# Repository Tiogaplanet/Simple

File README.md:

# Simple

 Simple - The Arduino UNO-compatible development system
 
 Created using pin-through hole (PTH) components, Simple is meant to be easy to assemble and modify.  This repository contains the Eagle files necessary to order the printed circuit board.

Based on Sparkfun's retired RedBoard PTH kit.

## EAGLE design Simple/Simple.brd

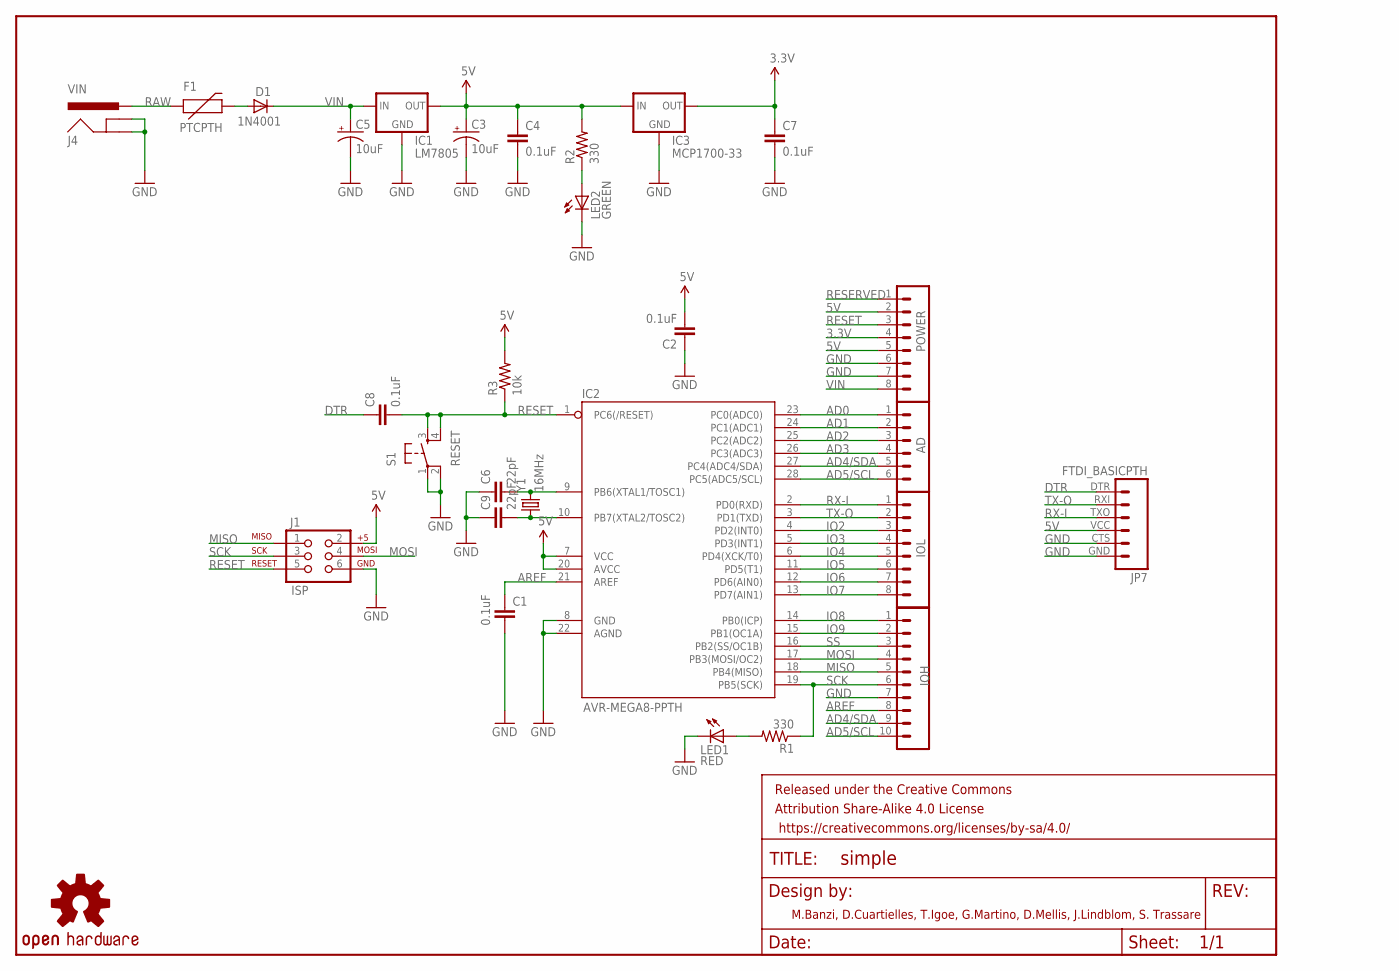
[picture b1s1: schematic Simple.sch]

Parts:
AD: M06SIP; 1X06
C1, C2, C4, C7, C8: 0.1uF; CAP-PTH-SMALL2
C3, C5: 10uF; CPOL-RADIAL-10UF-25V
C6, C9: 22pF; CAP-PTH-SMALL2
D1: 1N4001; DIODE-1N4001
F1: PTCPTH; PTC
FRAME2: FRAME-LETTER; CREATIVE_COMMONS
IC1: LM7805; TO-220-ALT
IC2: AVR-MEGA8-PPTH; DIL28-3
IC3: MCP1700-33; TO-92
IOH: IOH; 1X10
IOL: M081X08; 1X08
J1: ISP; 2X3
J4: VIN; POWER_JACK_PTH_LOCK
JP7: FTDI_BASICPTH; FTDI_BASIC
LED1: RED; LED5MM
LED2: GREEN; LED5MM
POWER: POWER; 1X08
R1, R2: 330; AXIAL-0.3
R3: 10k; AXIAL-0.3
S1: RESET; TACTILE-PTH
U$7: OSHW-LOGOM; OSHW-LOGO-M
Y1: 16MHz; HC49US

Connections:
3.3V: C7.1, IC3.3 (OUT), POWER.4
5V: C2.2, C3.1 (+), C4.1, IC1.OUT, IC2.7 (VCC), IC2.20 (AVCC), IC3.2 (IN), J1.2, JP7.VCC (4), POWER.5, R2.P$2 (2), R3.P$2 (2)
AD0: AD.1, IC2.23 (PC0(ADC0))
AD1: AD.2, IC2.24 (PC1(ADC1))
AD2: AD.3, IC2.25 (PC2(ADC2))
AD3: AD.4, IC2.26 (PC3(ADC3))
AD4/SDA: AD.5, IC2.27 (PC4(ADC4/SDA)), IOH.9
AD5/SCL: AD.6, IC2.28 (PC5(ADC5/SCL)), IOH.10
AREF: C1.1, IC2.21 (AREF), IOH.8
DTR: C8.1, JP7.DTR (1)
GND: C1.2, C2.1, C3.2 (-), C4.2, C5.2 (-), C6.1, C7.2, C9.1, IC1.GND, IC2.8 (GND), IC2.22 (AGND), IC3.1 (GND), IOH.7, J1.6, J4.GND, J4.GNDBREAK, JP7.CTS (5), JP7.GND (6), LED1.K (C), LED2.K (C), POWER.6, POWER.7, S1.1, S1.2
IO2: IC2.4 (PD2(INT0)), IOL.3
IO3: IC2.5 (PD3(INT1)), IOL.4
IO4: IC2.6 (PD4(XCK/T0)), IOL.5
IO5: IC2.11 (PD5(T1)), IOL.6
IO6: IC2.12 (PD6(AIN0)), IOL.7
IO7: IC2.13 (PD7(AIN1)), IOL.8
IO8: IC2.14 (PB0(ICP)), IOH.1
IO9: IC2.15 (PB1(OC1A)), IOH.2
MISO: IC2.18 (PB4(MISO)), IOH.5, J1.1
MOSI: IC2.17 (PB3(MOSI/OC2)), IOH.4, J1.4
unnamed: LED1.A, R1.P$2 (2)
unnamed: LED2.A, R2.P$1 (1)
unnamed: C6.2, IC2.9 (PB6(XTAL1/TOSC1)), Y1.2
unnamed: C9.2, IC2.10 (PB7(XTAL2/TOSC2)), Y1.1
unnamed: D1.A, F1.P$2 (2)
RAW: F1.P$1 (1), J4.PWR
RESERVED: POWER.1
RESET: C8.2, IC2.1 (PC6(/RESET)), J1.5, POWER.3, R3.P$1 (1), S1.3, S1.4
RX-I: IC2.2 (PD0(RXD)), IOL.1, JP7.TXO (3)
SCK: IC2.19 (PB5(SCK)), IOH.6, J1.3, R1.P$1 (1)
SS: IC2.16 (PB2(SS/OC1B)), IOH.3
TX-O: IC2.3 (PD1(TXD)), IOL.2, JP7.RXI (2)
VIN: C5.1 (+), D1.C, IC1.IN, POWER.8

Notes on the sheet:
M.Banzi, D.Cuartielles, T.Igoe, G.Martino, D.Mellis, J.Lindblom, S. Trassare

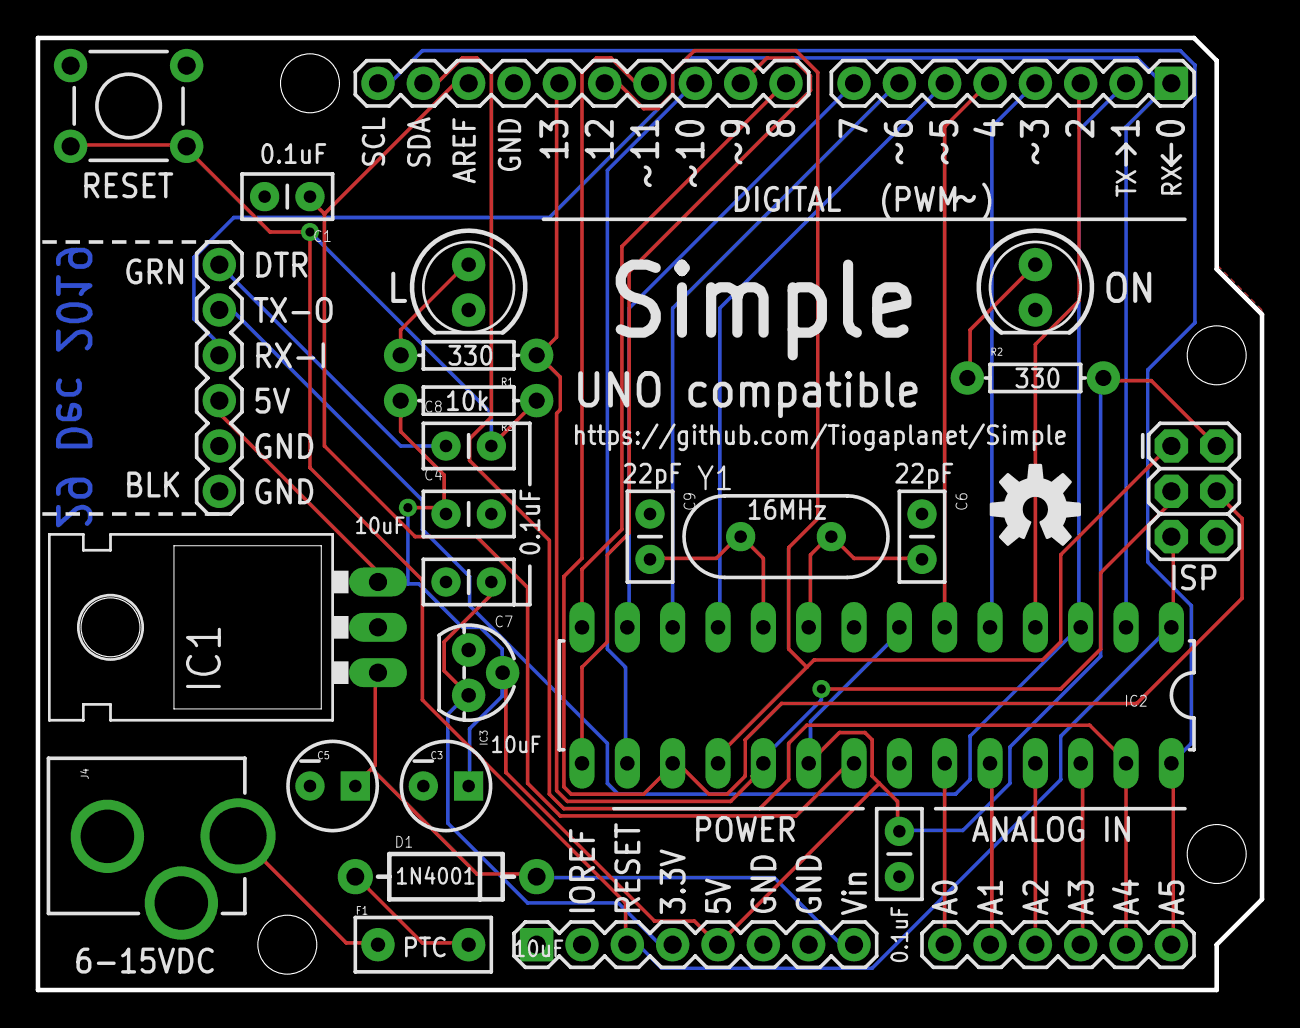
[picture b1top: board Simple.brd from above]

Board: 2 copper layers, 68.6 x 53.3 mm, 34 parts (0 on the bottom side), 33 nets.

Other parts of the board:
JP1, JP2, JP3, JP6: STAND-OFF

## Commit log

2019-12-29 Initial commit
    Be it called my own modification. My take on the Arduino UNO board. Based on Sparkfun's retired RedBoard PTH kit.
2019-12-30 Added IOREF and reserved pins

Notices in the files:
parts and their libraries:
SparkFun-Connectors: Licensing: Creative Commons ShareAlike 4.0 International - https://creativecommons.org/licenses/by-sa/4.0
SparkFun-Aesthetics: Released under the Creative Commons Attribution Share-Alike 4.0 License
SparkFun-Aesthetics: https://creativecommons.org/licenses/by-sa/4.0
